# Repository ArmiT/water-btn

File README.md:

### Smart button

Developed on ESP8266(07).

#### Get started
* Copy `firmware/config.example.lua` to `firmware/config.lua`.
* Add credentials for you wifi access points and mqtt.
* Upload scripts on board using converter from usb to uart/ttl (for ex. cp2102) and ESPLorer.

##### Cable pinout (see image)
1. DTR
2. TX
3. RX
4. VCC
5. nc (not connected)
6. GND

Additional you should connect RST to the JP1

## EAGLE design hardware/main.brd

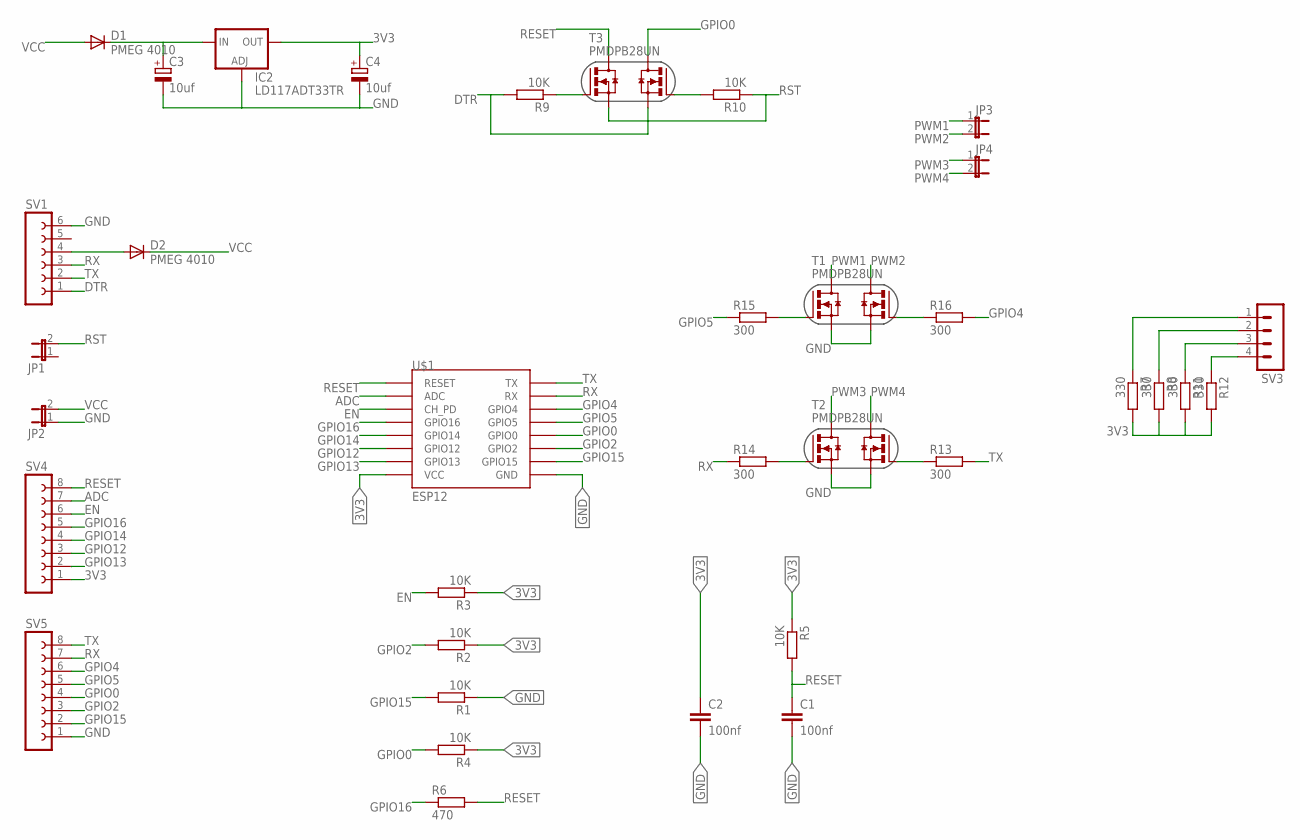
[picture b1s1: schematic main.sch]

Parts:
C1, C2: 100nf; C0805K
C3, C4: 10uf; SMC_B
D1, D2: PMEG 4010; SOD-323
IC2: LD117ADT33TR; DPACK
JP1, JP2, JP3, JP4: JUMPER-2PTH; 1X02
R1, R2, R3, R4, R5, R9, R10: 10K; R1206
R6: 470; R1206
R7, R8, R11, R12: 330; R1206
R13, R14, R15, R16: 300; R1206
SV1: FE06-1; FE06
SV3: MA04-1
SV4, SV5: FE08-1; FE08
T1, T2, T3: PMDPB28UN; SOT1118
U$1: ESP12

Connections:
3V3: C2.1, C4.+, IC2.4 (OUT), R2.1, R3.1, R4.1, R5.1, R7.2, R8.2, R11.2, R12.2, SV4.1, U$1.VCC
ADC: SV4.7, U$1.ADC
DTR: R9.2, SV1.1, T3.S2
EN: R3.2, SV4.6, U$1.CH_PD
GND: C1.2, C2.2, C3.-, C4.-, IC2.1 (ADJ), JP2.1, R1.1, SV1.6, SV5.1, T1.S1, T1.S2, T2.S1, T2.S2, U$1.GND
GPIO0: R4.2, SV5.4, T3.D2, T3.D22 (D2), U$1.GPIO0
GPIO2: R2.2, SV5.3, U$1.GPIO2
GPIO4: R16.2, SV5.6, U$1.GPIO4
GPIO5: R15.1, SV5.5, U$1.GPIO5
GPIO12: SV4.3, U$1.GPIO12
GPIO13: SV4.2, U$1.GPIO13
GPIO14: SV4.4, U$1.GPIO14
GPIO15: R1.2, SV5.2, U$1.GPIO15
GPIO16: R6.1, SV4.5, U$1.GPIO16
unnamed: R15.2, T1.G1
unnamed: R16.1, T1.G2
unnamed: R9.1, T3.G1
unnamed: R10.2, T3.G2
unnamed: R14.2, T2.G1
unnamed: R13.1, T2.G2
unnamed: D2.2 (A), SV1.4
unnamed: R12.1, SV3.4
unnamed: R11.1, SV3.3
unnamed: R8.1, SV3.2
unnamed: R7.1, SV3.1
PWM1: JP3.1, T1.D1, T1.D11 (D1)
PWM2: JP3.2, T1.D2, T1.D22 (D2)
PWM3: JP4.1, T2.D1, T2.D11 (D1)
PWM4: JP4.2, T2.D2, T2.D22 (D2)
RESET: C1.1, R5.2, R6.2, SV4.8, T3.D1, T3.D11 (D1), U$1.RESET
RST: JP1.2, R10.1, T3.S1
RX: R14.1, SV1.3, SV5.7, U$1.RX
TX: R13.2, SV1.2, SV5.8, U$1.TX
VCC: C3.+, D1.1 (C), D1.2 (A), D2.1 (C), IC2.3 (IN), JP2.2

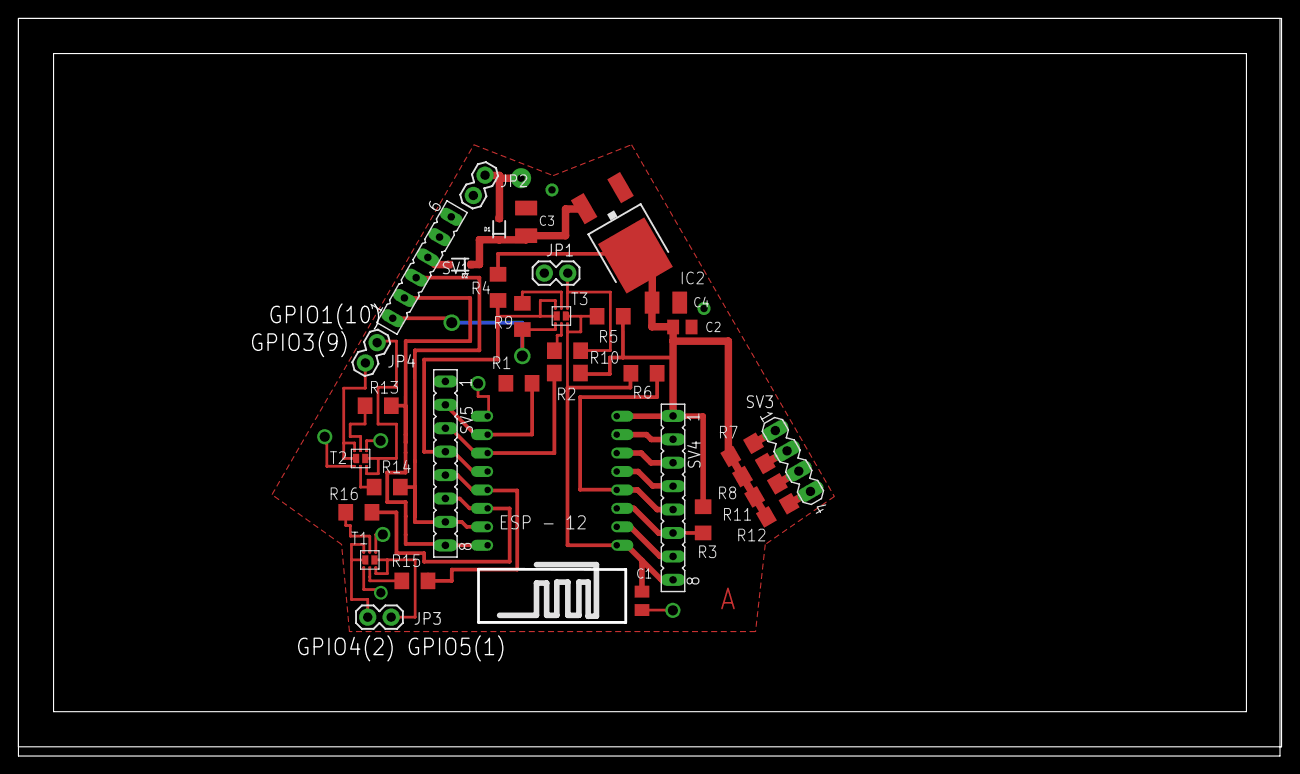
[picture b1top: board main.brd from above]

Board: 2 copper layers, 136.7 x 79.7 mm, 35 parts (0 on the bottom side), 34 nets.

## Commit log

2017-08-24 Initial
2017-08-24 Add description

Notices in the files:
parts and their libraries:
SparkFun: Licensing: CC v3.0 Share-Alike You are welcome to use this library for commercial purposes.
